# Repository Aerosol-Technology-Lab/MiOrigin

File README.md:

# MiOrigin
This device is a controller for a bioaerosol collector used by the [Aerosol Technology Lab](https://aerosoltechnologylab.tamu.edu/) of the Biological and Agricultural Engineering Department at Texas A&M University. The MiOrigin controller mimics the MiClone software, which requires a PC connection to use.
 
 ### Features
 - ESP32-WROOM-32E (16MB) MCU
 - 3.5" 480x320 touch-enabled LCD
 - Rechargeable 1000mAh LiPo battery via USB-C connector
 - Built-in male RS-232 port (MAX3232 RS-232 Line Driver) 
 - Over-the-air (OTA) update via BLE

## Branches

## USB Drivers for Windows, Linux, macOS
Install CP210x driver if device cannot be detected by computer if connecting to the controller via USB

- Download [CP210x Drivers](https://www.silabs.com/developers/usb-to-uart-bridge-vcp-drivers)

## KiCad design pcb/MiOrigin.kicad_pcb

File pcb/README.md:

# MiOrigin Controller PCB
PCB Schematic and Layour for MiOrigin Controller designed on KiCad

## Revisions
### Rev 1.1 
#### Updates since past revision (Rev 1.0)
1. Moved protection USB diodes to the front of the board
1. Replaced wrong footprint with correct size for the Tri-State Buffer (see Rev 1.0-Known Issue #2)

#### Known Issues
1. RS-232 TX and RX line are switched between the MAX-3232 IC and the D-Sub port. Continuing issue from previous revision (see Rev 1.0-Known Issue #1)

### Rev 1.0
#### Known Issues
1. RS-232 TX and RX line are switched between the MAX-3232 IC and the D-Sub port
1. Footprint for Tri-State Buffer is smaller than actual IC. Careful soldering is required

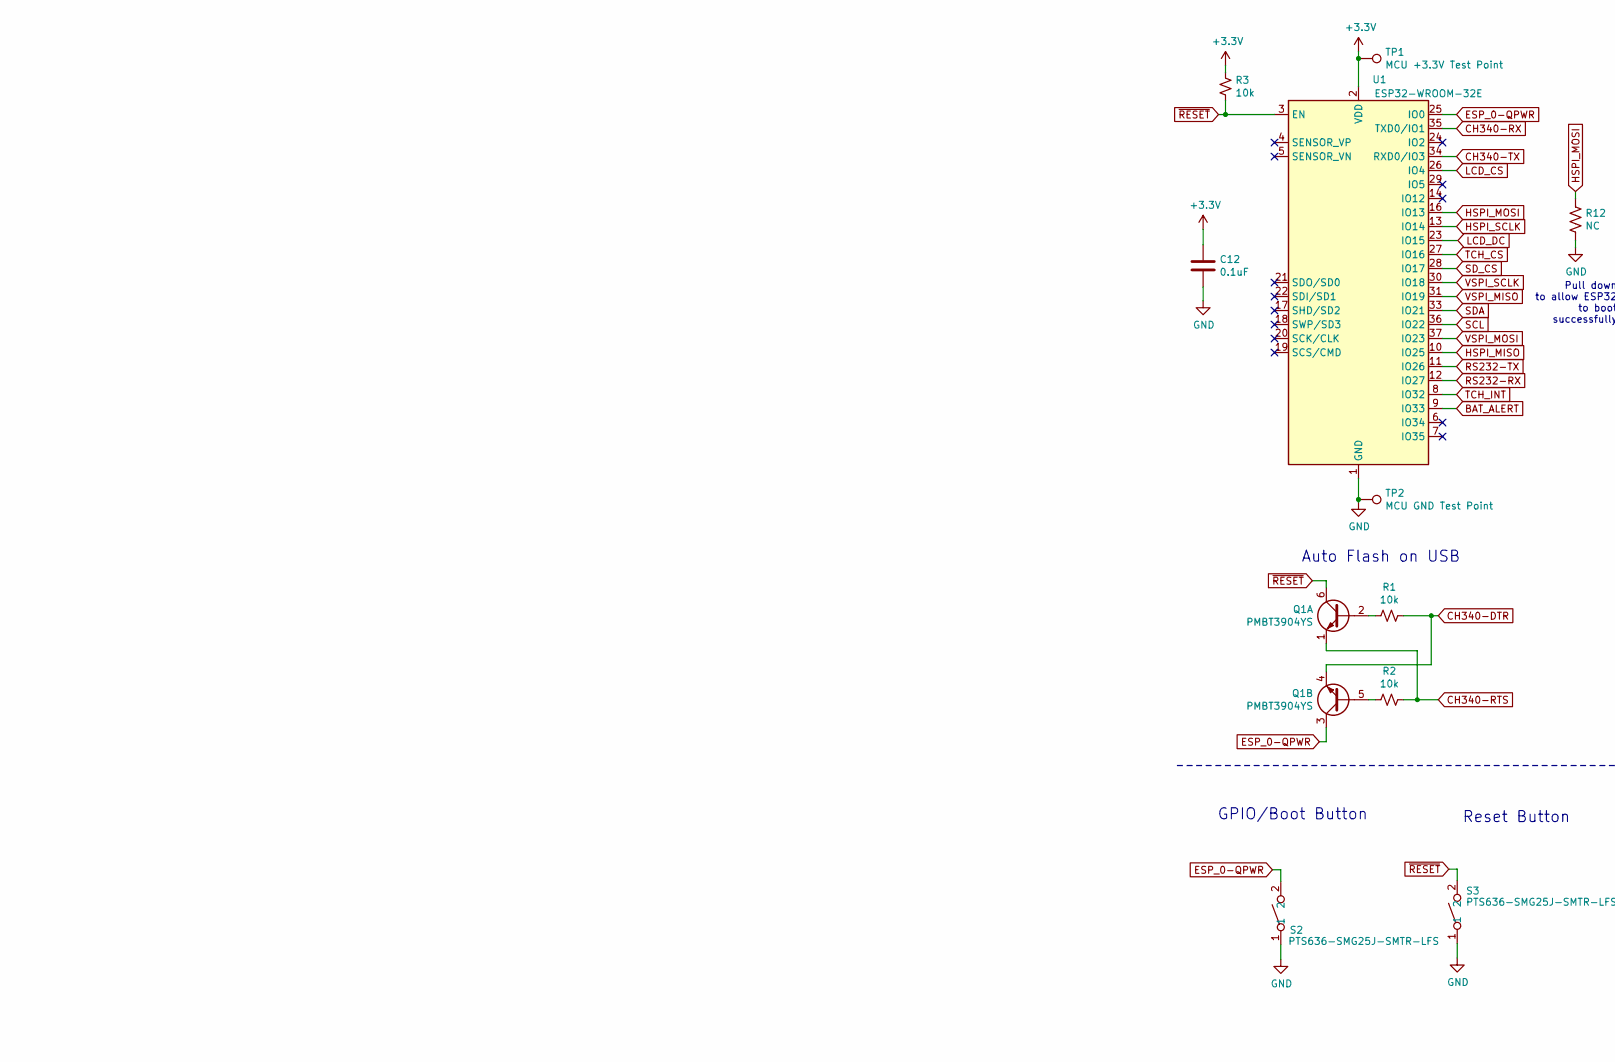
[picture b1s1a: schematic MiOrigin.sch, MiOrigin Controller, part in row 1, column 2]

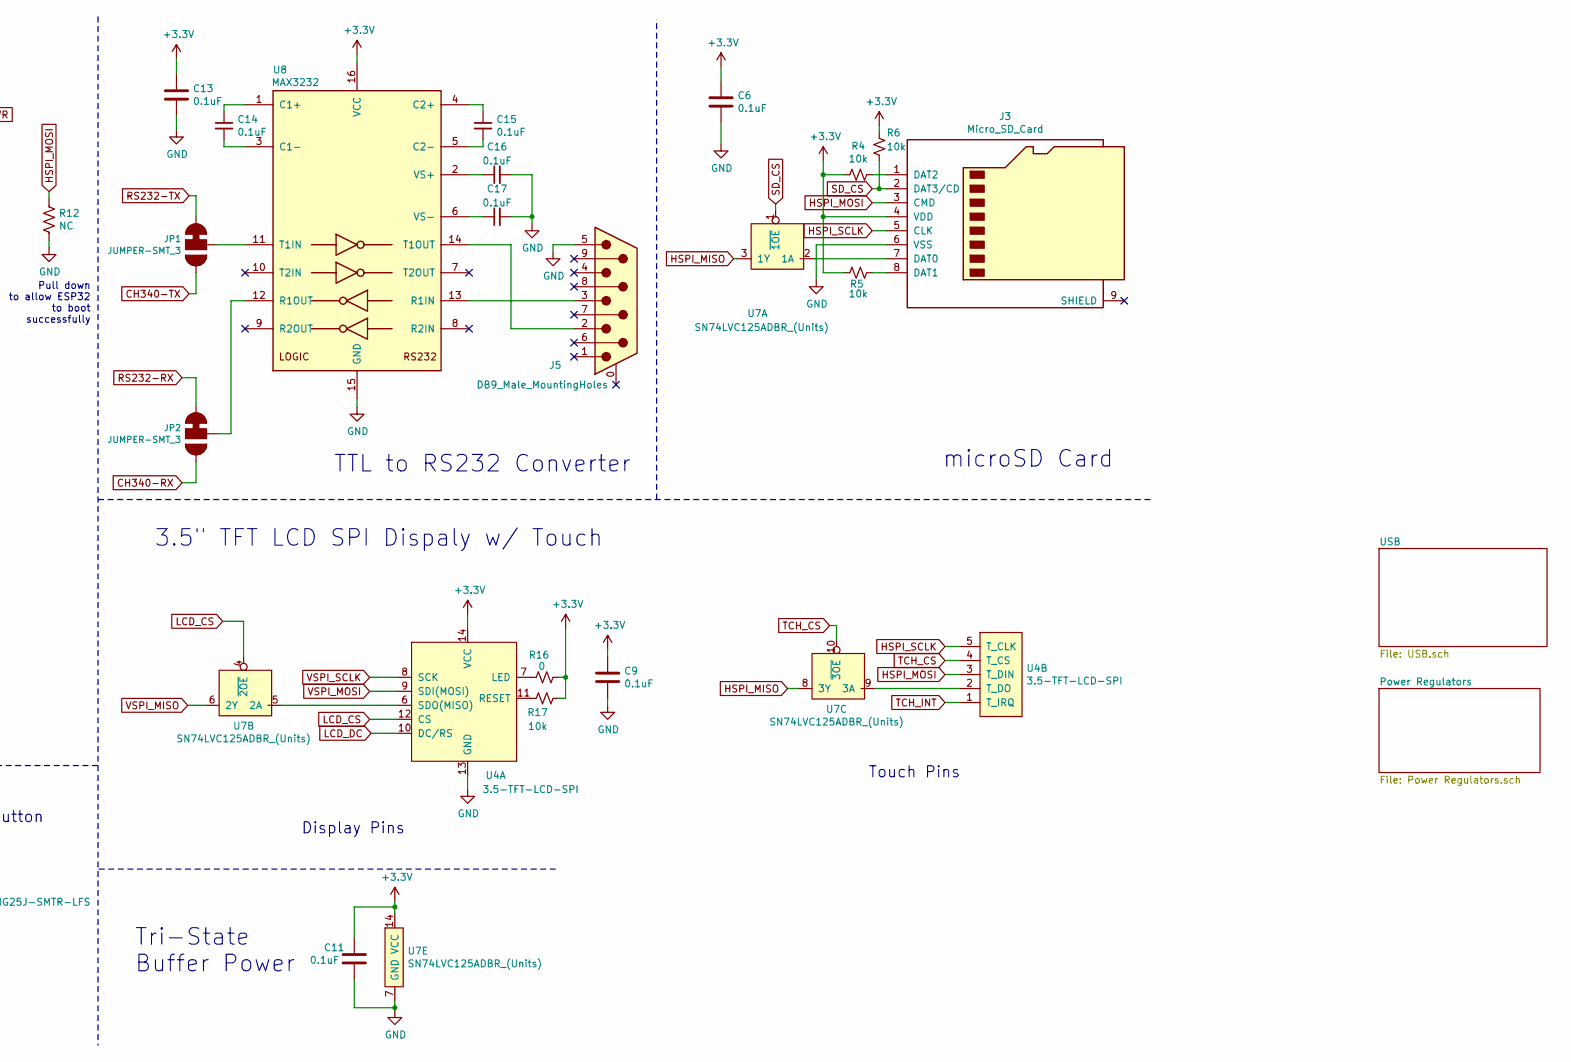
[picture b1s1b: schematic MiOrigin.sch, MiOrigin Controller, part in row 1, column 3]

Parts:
C6, C9, C11, C12, C13, C14, C15, C16, C17: 0.1uF; C_0603_1608Metric
J3: Micro_SD_Card; HRS_DM3CS-SF
J5: DB9_Male_MountingHoles; DB9_MALE; MPN LD09P33E4GX00LF
JP1, JP2: JUMPER-SMT_3; SolderJumper-3_P1.3mm_Bridged12_RoundedPad1.0x1.5mm
Q1: PMBT3904YS; SOT-363_SC-70-6
R1, R2, R3, R4, R5, R6, R17: 10k; R_0603_1608Metric
R12: NC; R_0603_1608Metric
R16: 0; R_0603_1608Metric
S2, S3: PTS636-SMG25J-SMTR-LFS; PTS636SK50SMTRLFS
TP1: MCU +3.3V Test Point; TestPoint_Pad_D2.0mm
TP2: MCU GND Test Point; TestPoint_Pad_D2.0mm
U1: ESP32-WROOM-32E; ESP32-WROOM-32; MPN ESP32-WROOM-32E (4MB HIGH TEMP)
U4: 3.5-TFT-LCD-SPI
U7: SN74LVC125ADBR_(Units); TSSOP-14_4.4x5mm_P0.65mm
U8: MAX3232; SOIC127P1030X265-16N; MPN MAX3232EIDWR

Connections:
+3V3: C6.1, C9.1, C11.1, C12.1, C13.1, J3.4 (VDD), R3.1, R4.2, R5.2, R6.2, R16.1, R17.1, TP1.1, U1.2 (VDD), U4.14 (VCC), U7.14 (VCC), U8.16 (VCC); also elsewhere on the board
BAT_ALERT: U1.9 (IO33); also elsewhere on the board
CH340-DTR: Q1.4 (E2), R1.1; also elsewhere on the board
CH340-RTS: Q1.1 (E1), R2.1; also elsewhere on the board
CH340-RX: JP2.3, U1.35 (TXD0/IO1); also elsewhere on the board
CH340-TX: JP1.3, U1.34 (RXD0/IO3); also elsewhere on the board
ESP_0-QPWR: Q1.3 (C2), S2.2, U1.25 (IO0)
GND: C6.2, C9.2, C11.2, C12.2, C13.2, C16.2, C17.2, J3.6 (VSS), J5.5, R12.2, S2.1, S3.1, TP2.1, U1.1 (GND), U1.15 (GND), U1.38 (GND), U1.39 (GND), U4.13 (GND), U7.7 (GND), U8.15 (GND); also elsewhere on the board
HSPI_MISO: U1.10 (IO25), U7.3 (1Y), U7.8 (3Y)
HSPI_MOSI: J3.3 (CMD), R12.1, U1.16 (IO13), U4.3 (T_DIN)
HSPI_SCLK: J3.5 (CLK), U1.13 (IO14), U4.5 (T_CLK)
LCD_CS: U1.26 (IO4), U4.12 (CS), U7.4 (~2OE)
LCD_DC: U1.23 (IO15), U4.10 (DC/RS)
unnamed: C14.1, U8.1 (C1+)
unnamed: C14.2, U8.3 (C1-)
unnamed: C15.1, U8.4 (C2+)
unnamed: C15.2, U8.5 (C2-)
unnamed: C16.1, U8.2 (VS+)
unnamed: C17.1, U8.6 (VS-)
unnamed: J3.1 (DAT2), R4.1
unnamed: J3.7 (DAT0), U7.2 (1A)
unnamed: J3.8 (DAT1), R5.1
unnamed: J5.2, U8.14 (T1OUT)
unnamed: J5.3, U8.13 (R1IN)
unnamed: JP1.2, U8.11 (T1IN)
unnamed: JP2.2, U8.12 (R1OUT)
unnamed: Q1.2 (B1), R1.2
unnamed: Q1.5 (B2), R2.2
unnamed: R16.2, U4.7 (LED)
unnamed: R17.2, U4.11 (RESET)
unnamed: U4.2 (T_DO), U7.9 (3A)
unnamed: U4.6 (SDO(MISO)), U7.5 (2A)
RS232-RX: JP2.1, U1.12 (IO27)
RS232-TX: JP1.1, U1.11 (IO26)
SCL: U1.36 (IO22); also elsewhere on the board
SDA: U1.33 (IO21); also elsewhere on the board
SD_CS: J3.2 (DAT3/CD), R6.1, U1.28 (IO17), U7.1 (~1OE)
TCH_CS: U1.27 (IO16), U4.4 (T_CS), U7.10 (~3OE)
TCH_INT: U1.8 (IO32), U4.1 (T_IRQ)
VSPI_MISO: U1.31 (IO19), U7.6 (2Y)
VSPI_MOSI: U1.37 (IO23), U4.9 (SDI(MOSI))
VSPI_SCLK: U1.30 (IO18), U4.8 (SCK)
~RESET: Q1.6 (C1), R3.2, S3.2, U1.3 (EN)

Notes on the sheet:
microSD Card
Pull down to allow ESP32 to boot successfully
GPIO/Boot Button
Reset Button
Tri-State Buffer Power
Auto Flash on USB
TTL to RS232 Converter
3.5" TFT LCD SPI Dispaly w/ Touch
Touch Pins
Display Pins

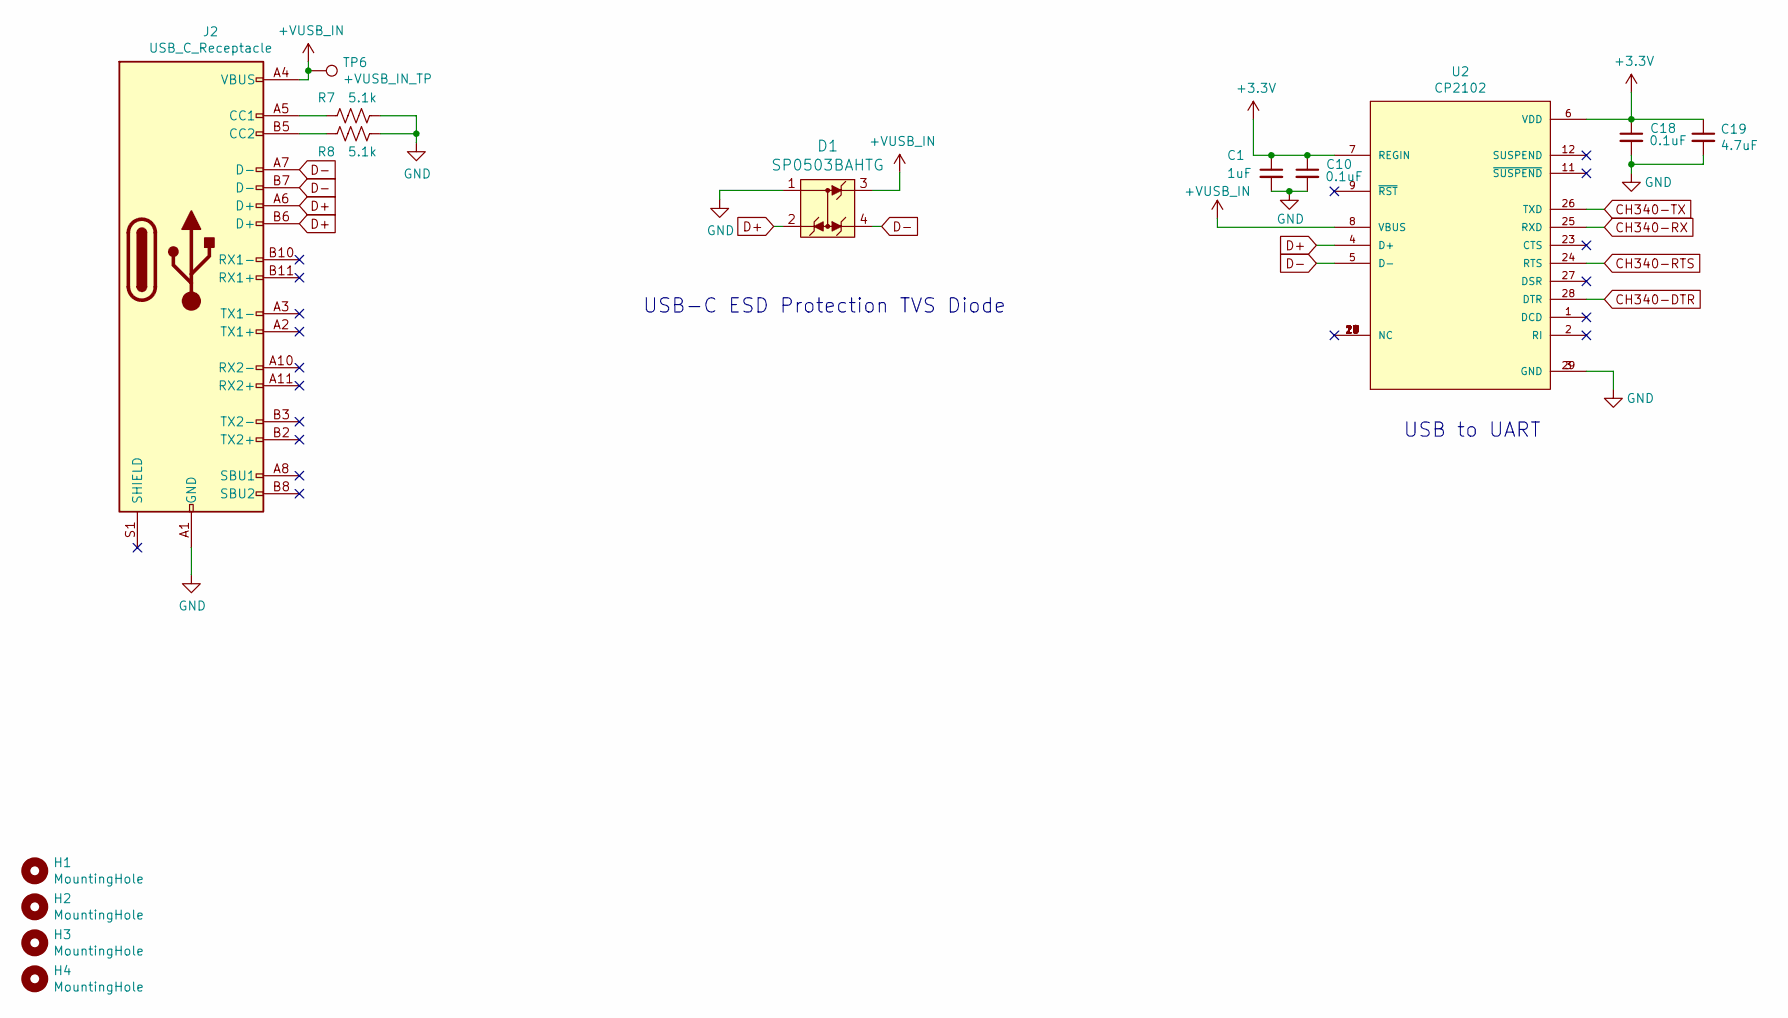
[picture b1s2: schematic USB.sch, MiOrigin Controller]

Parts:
C1: 1uF; C_0603_1608Metric
C10, C18: 0.1uF; C_0603_1608Metric
C19: 4.7uF; C_0805_2012Metric
D1: SP0503BAHTG; SOT-143-4; MPN SP0503BAHTG; Digi-Key_PN F2715CT-ND
H1, H2, H3, H4: MountingHole; MountingHole_3.2mm_M3_DIN965_Pad_TopBottom
J2: USB_C_Receptacle; USB_C_Receptacle_GCT_USB4085; MPN USB4085-GF-A
R7, R8: 5.1k; R_0603_1608Metric
TP6: +VUSB_IN_TP; TestPoint_Pad_D2.0mm
U2: CP2102; QFN50P500X500X100-29N

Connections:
+3V3: C1.1, C10.1, C18.1, C19.1, U2.6 (VDD), U2.7 (REGIN); also elsewhere on the board
+VUSB_IN: D1.3, J2.A4 (VBUS), J2.A9 (VBUS), J2.B4 (VBUS), J2.B9 (VBUS), TP6.1, U2.8 (VBUS); also elsewhere on the board
CH340-DTR: U2.28 (DTR); also elsewhere on the board
CH340-RTS: U2.24 (RTS); also elsewhere on the board
CH340-RX: U2.25 (RXD); also elsewhere on the board
CH340-TX: U2.26 (TXD); also elsewhere on the board
D+: D1.2, J2.A6 (D+), J2.B6 (D+), U2.4 (D+)
D-: D1.4, J2.A7 (D-), J2.B7 (D-), U2.5 (D-)
GND: C1.2, C10.2, C18.2, C19.2, D1.1, J2.A1 (GND), J2.A12 (GND), J2.B1 (GND), J2.B12 (GND), R7.1, R8.1, U2.3 (GND), U2.29 (GND); also elsewhere on the board
unnamed: J2.A5 (CC1), R7.2
unnamed: J2.B5 (CC2), R8.2
unnamed: U2.10 (NC), U2.13 (NC), U2.14 (NC), U2.15 (NC), U2.16 (NC), U2.17 (NC), U2.18 (NC), U2.19 (NC), U2.20 (NC), U2.21 (NC), U2.22 (NC)

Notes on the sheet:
USB-C ESD Protection TVS Diode
USB to UART

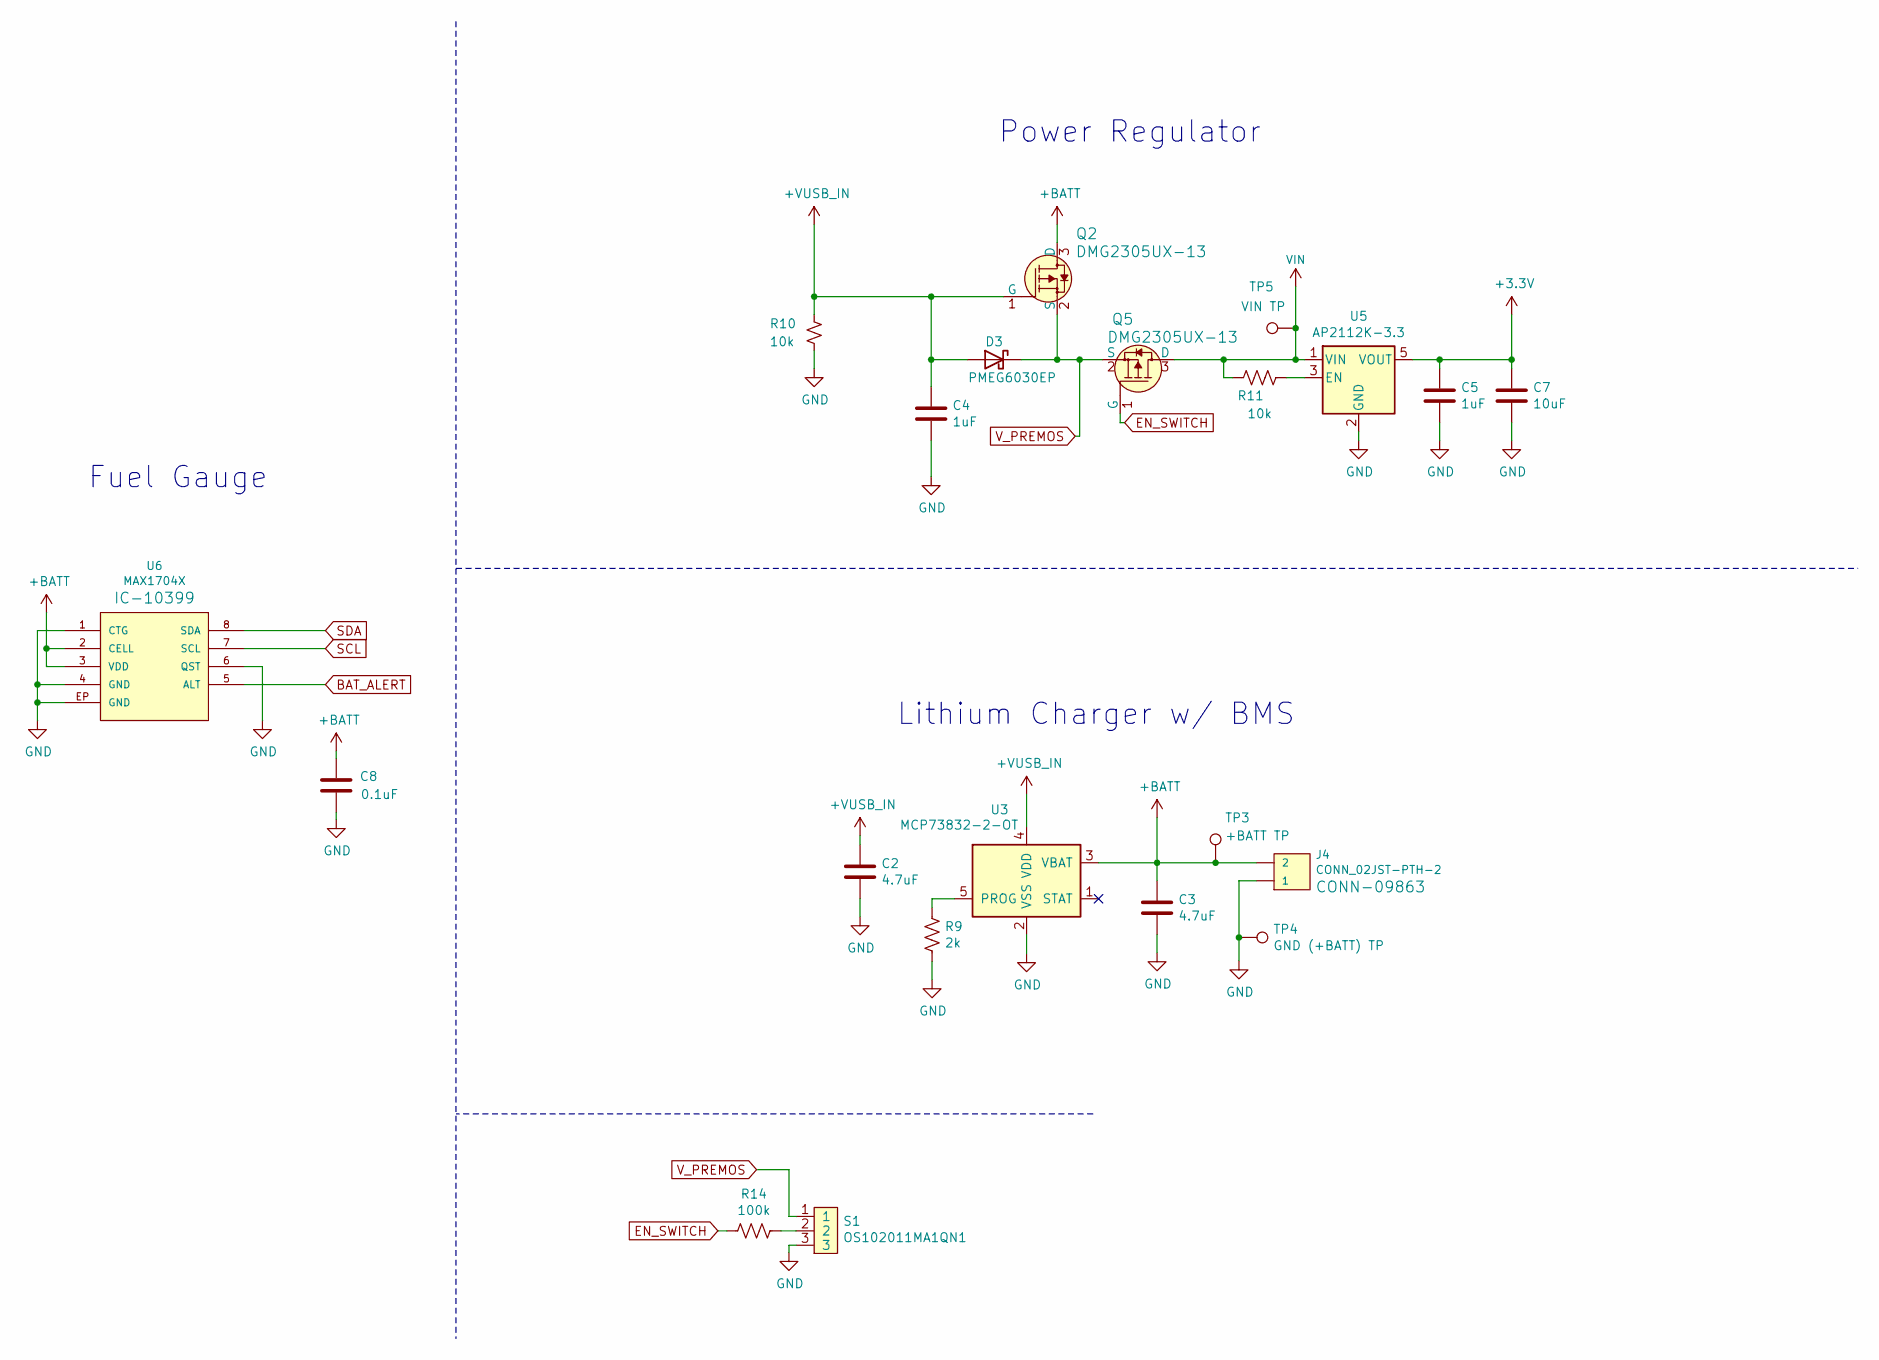
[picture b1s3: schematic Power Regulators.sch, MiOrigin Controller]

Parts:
C2, C3: 4.7uF; C_0805_2012Metric
C4, C5: 1uF; C_0603_1608Metric
C7: 10uF; C_1206_3216Metric
C8: 0.1uF; C_0603_1608Metric
D3: PMEG6030EP; D_SOD-128; MPN PMEG6030EP,115
J4: CONN_02JST-PTH-2; JST-2-PTH
Q2, Q5: DMG2305UX-13; SOT-23-3; MPN DMG2305UX-13; Digi-Key_PN DMG2305UX-13DICT-ND
R9: 2k; R_0603_1608Metric
R10, R11: 10k; R_0603_1608Metric
R14: 100k; R_0603_1608Metric
S1: OS102011MA1QN1
TP3: +BATT TP; TestPoint_Pad_D2.0mm
TP4: GND (+BATT) TP; TestPoint_Pad_D2.0mm
TP5: VIN TP; TestPoint_Pad_D2.0mm
U3: MCP73832-2-OT; SOT-23-5
U5: AP2112K-3.3; SOT-23-5
U6: MAX1704X; SON50P200X200X80-9N; MPN MAX17048G+T10

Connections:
+3V3: C5.1, C7.1, U5.5 (VOUT); also elsewhere on the board
+BATT: C3.1, C8.2, J4.2, Q2.3 (D), TP3.1, U3.3 (VBAT), U6.2 (CELL), U6.3 (VDD)
+VUSB_IN: C2.1, C4.1, D3.2 (A), Q2.1 (G), R10.1, U3.4 (VDD); also elsewhere on the board
BAT_ALERT: U6.5 (ALT); also elsewhere on the board
EN_SWITCH: Q5.1 (G), R14.2
GND: C2.2, C3.2, C4.2, C5.2, C7.2, C8.1, J4.1, R9.2, R10.2, S1.3, TP4.1, U3.2 (VSS), U5.2 (GND), U6.1 (CTG), U6.4 (GND), U6.6 (QST), U6.EP (GND); also elsewhere on the board
unnamed: R9.1, U3.5 (PROG)
unnamed: R11.1, U5.3 (EN)
unnamed: R14.1, S1.2
SCL: U6.7 (SCL); also elsewhere on the board
SDA: U6.8 (SDA); also elsewhere on the board
VIN: Q5.3 (D), R11.2, TP5.1, U5.1 (VIN)
V_PREMOS: D3.1 (K), Q2.2 (S), Q5.2 (S), S1.1

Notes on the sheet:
Power Regulator
Fuel Gauge
Lithium Charger w/ BMS

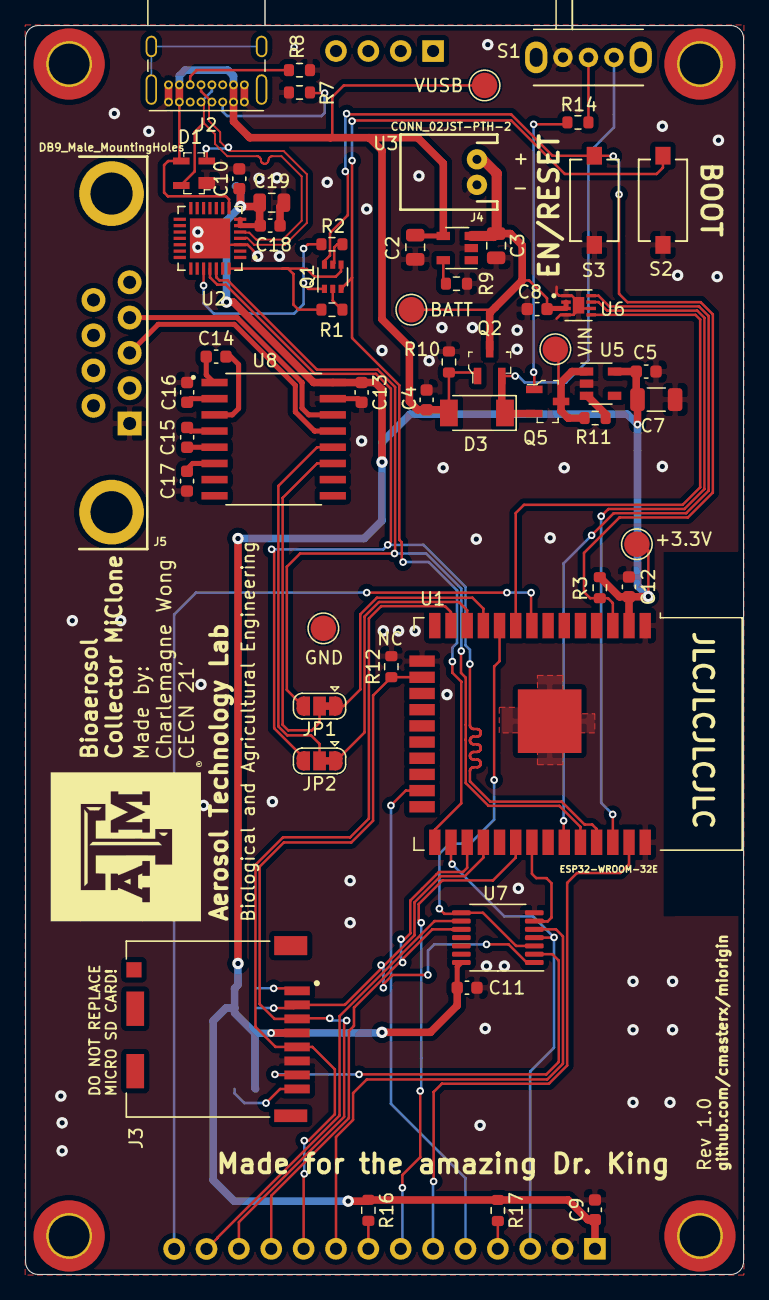
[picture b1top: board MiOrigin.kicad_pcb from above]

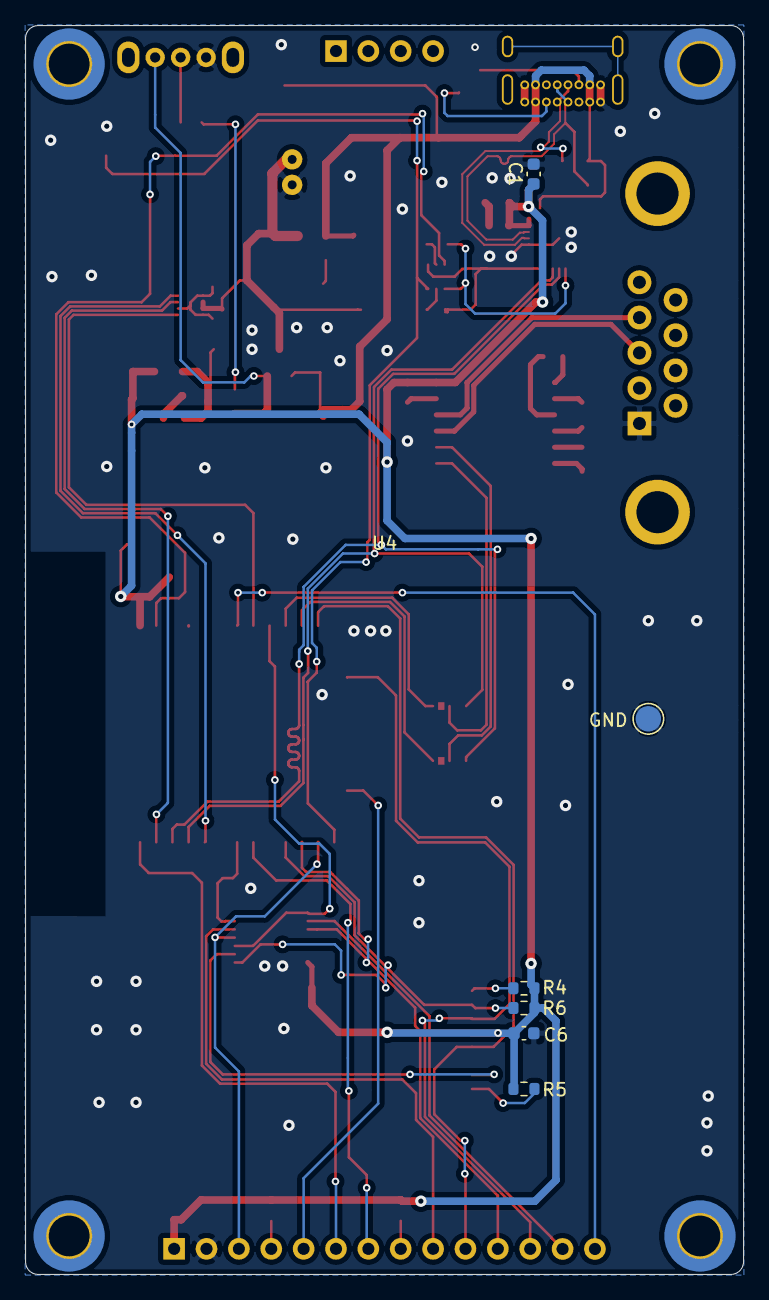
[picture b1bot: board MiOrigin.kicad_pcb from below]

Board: 2 copper layers, 56.3 x 98.0 mm, 66 parts (7 on the bottom side), 56 nets.

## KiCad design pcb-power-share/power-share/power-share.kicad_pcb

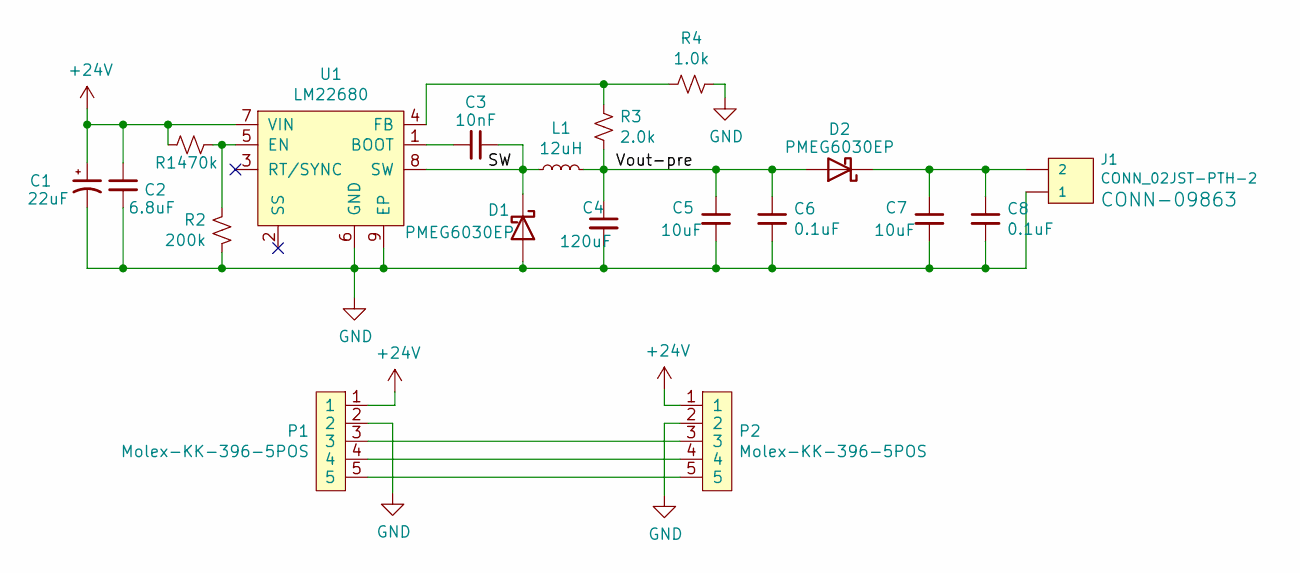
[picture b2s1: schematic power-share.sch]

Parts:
C1: 22uF; CP_Elec_8x6.5
C2: 6.8uF; C_1812_4532Metric
C3: 10nF; C_0402_1005Metric_Pad0.74x0.62mm_HandSolder
C4: 120uF; C_Elec_4x5.8
C5, C7: 10uF; C_0805_2012Metric
C6, C8: 0.1uF; C_0603_1608Metric
D1, D2: PMEG6030EP; D_SOD-128
J1: CONN_02JST-PTH-2; JST-2-PTH
L1: 12uH; L_Bourns_SRR1260
P1, P2: Molex-KK-396-5POS
R1: 470k; R_0603_1608Metric
R2: 200k; R_0603_1608Metric
R3: 2.0k; R_0603_1608Metric
R4: 1.0k; R_0603_1608Metric
U1: LM22680

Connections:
+24V: C1.1, C2.1, P1.1, P2.1, R1.1, U1.7 (VIN)
/SW: C3.1, D1.1 (K), L1.1, U1.8 (SW)
/Vout-pre: C4.1, C5.1, C6.1, D2.2 (A), L1.2, R3.2
GND: C1.2, C2.2, C4.2, C5.2, C6.2, C7.2, C8.2, D1.2 (A), J1.1, P1.2, P2.2, R2.1, R4.1, U1.6 (GND), U1.9 (EP)
unnamed: C3.2, U1.1 (BOOT)
unnamed: C7.1, C8.1, D2.1 (K), J1.2
unnamed: P1.3, P2.3
unnamed: P1.4, P2.4
unnamed: P1.5, P2.5
unnamed: R1.2, R2.2, U1.5 (EN)
unnamed: R3.1, R4.2, U1.4 (FB)

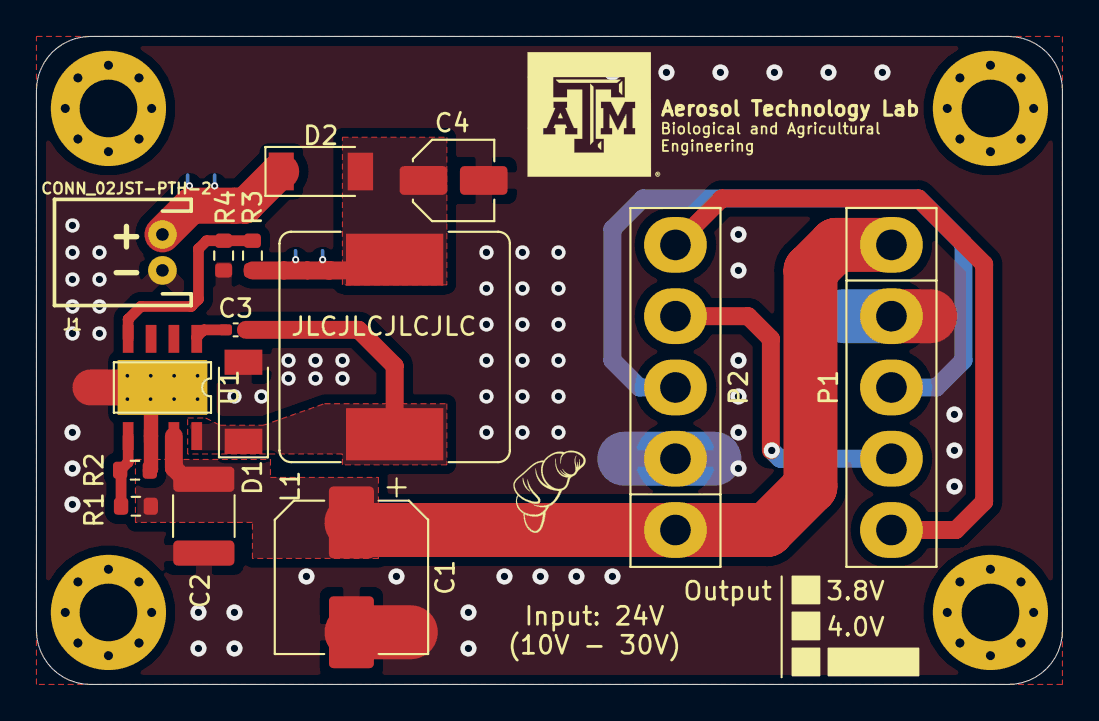
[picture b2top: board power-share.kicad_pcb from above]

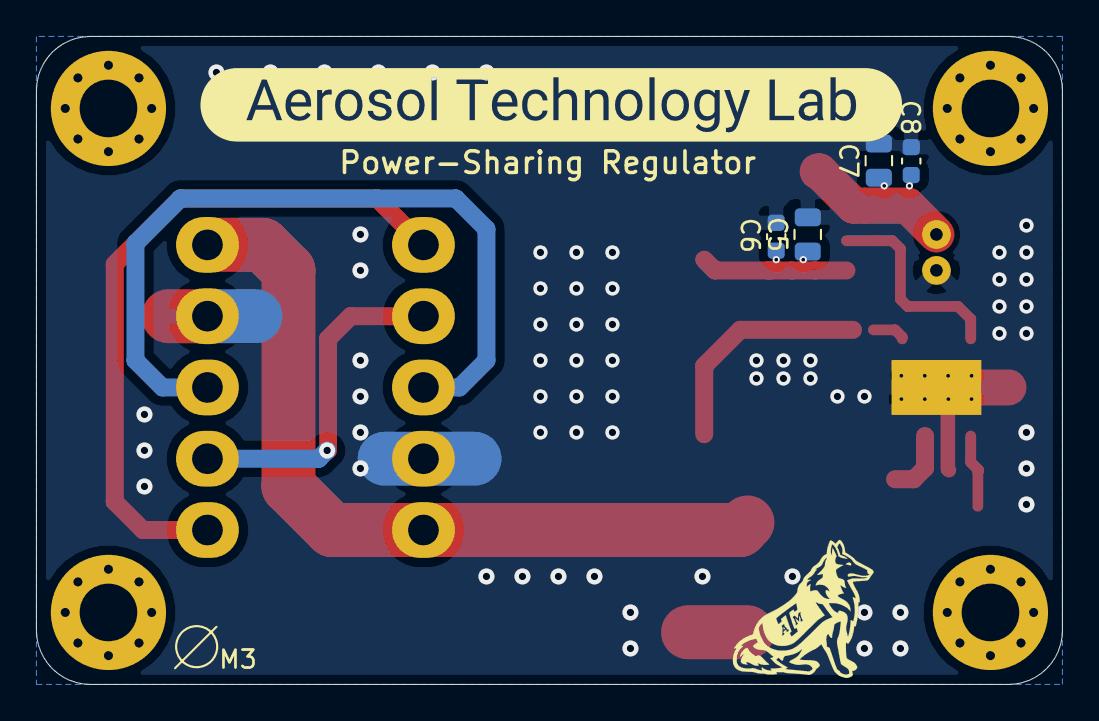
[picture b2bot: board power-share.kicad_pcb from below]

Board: 2 copper layers, 57.0 x 36.0 mm, 20 parts (5 on the bottom side), 11 nets.

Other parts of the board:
kibuzzard-61710895: G***; label

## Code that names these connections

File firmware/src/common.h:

// common properties shared by factory and ota firmware

#pragma once

#define RS232_RX2 27
#define RS232_TX2 26

#define I2C_SDA 21
#define I2C_SCL 22

#define VSPI_MISO MISO
#define VSPI_MOSI MOSI
#define VSPI_SCLK SCK
#define VSPI_SS 4

#define HSPI_MISO 25
#define HSPI_MOSI 13
#define HSPI_SCLK 14
#define HSPI_SS 17

#define SD_CS 17
#define LCD_CS 4
#define TCH_CS 16

#define LCD_DC 15

#define TCH_INT 32

#define LINE_TERMINATION    (uint16_t) 0x0D0A
#define FLUSH_SERIAL        (uint16_t) 0x0000

#include <Arduino.h>
#include <SPI.h>

extern SPIClass *vspi;
extern SPIClass *hspi;

void hardReset();

void Common_Init();

/**
 * @brief 
 * 
 * @param buffer 
 * @parstrcmpam stream 
 */
size_t readUntilEnd(char *buffer, size_t bufferSize, Stream &stream);

void Common_USBC_Handler(void *params);

void Common_HEX_print(char *cstr, Stream &stream = Serial);

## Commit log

2021-06-24 Initial push
2021-06-25 Replace USB to UART with CP2102-GM
2021-06-29 Create CNAME
2021-07-01 Update board
2021-07-01 Move pcb files to its own folder
2021-07-01 Add initial firmware
2021-07-03 Update board info
2021-07-03 Add README
2021-07-03 Add tests
2021-07-03 Add post scripts. Not working and disabled
2021-07-04 Add precompiled binaries
2021-07-04 Add post scripts after compile
2021-07-04 README update
2021-07-04 progress
2021-07-08 Add pdf schematic
2021-07-14 Update esp scripts
2021-07-14 Add build tasks (WIP)
2021-07-14 Continued development
2021-07-14 Update partition table
2021-07-16 Update post script runner
2021-07-16 update settings
2021-07-16 Add alpha binaries
2021-07-16 Working MicroSD card. Serial port issue at UART0 where the first 4 bits of the stream has a change of being deleted
2021-07-17 Add hard reset function
2021-07-17 Add option to boot directly to firmware
2021-07-17 Add data information about each device. Untested
2021-07-17 Enable BLE
2021-07-18 Add BLE wip functionality. Working
2021-07-19 Continue development of BLE package
2021-07-19 Add command to write to file from BLE buffer
2021-07-19 Fix error logs
2021-07-20 Add initial website
2021-07-20 Add build files
2021-07-20 Renamed build directory inside website project to root docs
2021-07-20 Begin moving files
2021-07-20 Add typescript support
2021-07-20 Convert to tsx
2021-07-20 Completed ts conversion
2021-07-21 Add feature that if requested bytes to write to file is 0, then write all of buffer
2021-07-21 Refactor 'receiverBuffer' to 'mainBuffer'
2021-07-21 Increase max packet size to 512 bytes
2021-07-21 Code cleanup
2021-07-21 Add debug flag to platformio environment
2021-07-21 Add descriptor to BLE
2021-07-24 Add tft lcd library
2021-07-27 Add XPT2046 Driver
2021-07-27 ../platformio.ini
2021-07-27 Add commented -O2 flag
2021-07-27 Clean up init code
2021-07-27 Add test XPT2046 Test Driver - not working
2021-07-27 Add new property to device info and cleanup code handling aquisition of device info
2021-07-27 Remove old code
2021-07-27 Fix print on touch screen data
2021-07-27 Fix compile warnings
2021-07-27 Add battery - MAX178048 driver
2021-07-27 Update platform.ini to include Sparkfun MAX17804x driver
2021-07-28 Clean up code and add new serial boot message
2021-07-28 Add help command
2021-07-30 Add new outline image
2021-07-31 Add WiFi manager to manage several WiFi connections, keep WiFi alive, and WiFi power savings
2021-07-31 Part of previous commit. This file was unintentionally omitted
2021-08-03 Fix no except
2021-08-03 Prettied up prints on serial and display
2021-08-03 Change method of acquiring message over usb
2021-08-03 Change how version numbers are handled
2021-08-03 Add firmware updater task
2021-08-03 Bug fix
2021-08-03 Add binaries with new meta file
2021-08-03 Add documentation to firmware updater task
2021-08-04 Add wpa2 enterprise credentials format
2021-08-04 Fix missing WiFiController definition, task holds, and stack overflow
2021-08-04 Working WPA implementation
2021-08-04 Move wifi system files to own folder
2021-08-04 I think the rs-232 is fixed
2021-08-04 Remove unused BLE callback
2021-08-04 Fix MicroSD bug by fixing pinout of RS-232 port
2021-08-04 Update firmware README removing items from known issues after bug fixes
2021-08-04 Cleanup code
2021-08-05 Few updates
2021-08-06 Add credentials template
2021-08-06 Add issue
2021-08-06 Add utils cpp
2021-08-06 Fix issues
2021-08-07 Fix mispelling mistakes
2021-08-07 Testing different mbedtls buffer sizes
2021-08-13 Add new page system in C
2021-08-14 Add config flags to enable WiFi and OTA updates
2021-08-14 Add WiP touch screen interrupt handler
2021-08-14 Add touch screen handler code
2021-08-14 Add documentation
2021-08-14 Update pagesystem
2021-08-14 Replace enum with bool
2021-08-15 Minor fixes
2021-08-15 Update board information to reflect useable RAM in ESP32-WROOM-32E (16MB)
2021-08-15 A lot
2021-08-15 Add dev macro for prints
2021-08-15 Update factory firmware to reflect new method of debug prints
2021-08-15 Fix file not closed when reading device information
2021-08-15 Fix touchscreen rotation
2021-08-15 Update how acquiring points work
2021-08-16 Working calibration screen
2021-08-16 Misc changes to prepare for code refactoring
2021-08-16 Fix calibration bug on the y-axis
2021-08-16 Add graphics handler for Pages
2021-08-17 Update graphics system and fix bugs in touchscreen driver
2021-08-17 Add debug page
2021-08-20 Button functionality updates
2021-08-24 Add code for WIP sockets
2021-08-25 Fix bug where delay is using the wrong macro
2021-08-25 Fix portmax delay bug
2021-08-25 WIP miclone emulation driver
2021-08-25 Update tft drivers to understand different orientations
2021-08-25 Begin updating buttons to reflect miclone emulation drivers
2021-08-25 Fix touchscreen bug from new implementation
2021-08-26 Update miclone driver
2021-08-26 Fix missing include
2021-08-26 Fix positioning for button text
2021-08-31 change firmware starting rate
2021-08-31 Rotated screen and bug fixes
2021-08-31 Fix button issue
2021-08-31 Remove unused code
2021-08-31 fix spelling change
2021-08-31 Misc changes - add calibration button
2021-09-01 Add number field component and everything along with it
2021-09-10 Add post touch digitizer handler
2021-09-10 Progress, runtime error with heap corruption
2021-09-10 Add more options to drawing wrapper
2021-09-10 Keypad works with heap crashes once in a while
2021-09-11 Bug fixes
2021-09-17 Works
2021-09-17 Applied conversion of how buttons are managed in memory
2021-09-17 Separated timer from a single text area with minutes and seconds to two separate text areas
2021-09-17 Remove non-functioning/deprecated classes
2021-09-17 Add clear button
2021-09-21 Add vscode settings for certain files
2021-09-21 UI improvements
2021-09-21 Bug fixes and added file logging support during debug mode
2021-09-21 Missing forward slash in file
2021-09-22 Add updated factory file
2021-09-22 Add flags to platform.io
2021-09-22 Misc changes
2021-09-22 comment unused code
2021-09-22 Add testing framework
2021-09-22 Add post tests
2021-09-22 Add RAII for mutex
2021-09-22 Does not work
2021-09-22 Add comment, pointing out issue
2021-09-22 Fix attempt with heap poisoning
2021-09-22 Fix timer bug
2021-09-24 Fix stack overflow error in miclone driver
2021-09-24 Add home page, everything works!
2021-09-24 Add feature to draw circle in application
2021-09-24 Add toggle button
2021-09-24 Add feature to allow sample and waste selection
2021-09-28 Add macro for enabling callibration
2021-09-28 Fix bug due to hardware issue in controller. The capacitors near the MAX3232 cannot hold its rated capacitance when it is charged near 15V (the IC charges the capacitors to 12V)
2021-10-29 Remove delay in touchscreen driver
2021-10-29 Add softAP controls to WiFi driver
2021-11-02 Add soft AP control
2022-01-04 Add remote binaries
2022-01-06 Misc changes to python post build script
2022-01-06 WIP stop button
2022-01-06 Driver fix
2022-01-06 Disable unused code
2022-01-11 Add flag to disable BLE
2022-01-11 Add compile flag (enabled via config.h) to enable sample waste toggle flag. This should be disabled
2022-01-11 Fix compile errors
2022-01-11 Add stop signal over serial port
2022-01-11 Disable dev debug for release
2022-01-11 Add run command for serial input
2022-01-11 Change print in stop signal to only display when dev debug mode is enabled
2022-01-11 Fix bug with improper command handling
2022-01-12 Clean up code
2023-08-12 Add experimental web features
2023-08-12 Add pcb powershare pcb
